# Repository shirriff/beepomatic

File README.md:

# beepomatic: automated backplane finding for Apollo-era hardware

This repository describes hardware and software for reverse-engineering a test box used with Apollo space hardware.
This is unlike to be useful to anyone else, but I figure I'll document it.

## Background

In the Apollo mission to the Moon, the [Up-Data Link](https://mobile.twitter.com/kenshirriff/status/1433169432709373953) was used to send data up to the spacecraft from
the ground.

To test the Up-Data Link, the [Up-Data Link Confidence Test Set](https://twitter.com/kenshirriff/status/1432411774985195527) was used.
Unfortunately, we can't find any documentation on this test box, so I'm reverse-engineering it.

The box consists of 25 circuit boards plugged into a wire-wrapped backplane. It's almost impossible to figure out how the boards are connected through this
tangle of wires. I beeped out some connections with a multimeter, but it is extremely tedious to do this manually through trial and error.
So I decided to automate the beeping process.

## Beep-o-matic

My idea was to build two boards that will automatically beep out the connections between them.
The idea is to pull one pin low and then see which other pins are pulled low on the other board; this indicates the pins are connected.

I still need to put boards into each combination of slots, so I need to run 300 scans. This is still somewhat tedious, but much better than probing the entire backplane
manually to find a single connection.

### Implementation

The backplane is implemented with 47-pin Elco connectors. Each board has three 16-bit GPIO chips connected to these pins; I used [PCA9555A](https://www.nxp.com/docs/en/data-sheet/PCA9555A.pdf) chips.)
The chips are driven over I2C from a Teensy microcontroller.
(Thanks to [PCBWay](https://www.pcbway.com/) for sponsoring these boards.)

On the software side, I wrote a simple program *beeper.ino*, which cycles through the 47 pins on each board, pulling each pin low in turn. It reads the remaining pins to see which ones are low
and outputs that data to the serial port. It takes under a second to perform this scan.

I run *beeper.py* on my laptop; it records the output for each scan in output files.

Finally, the program *net.py* processes these output files to find connected components and output the wiring nets.

### Issues

I pulled out all the boards, so I don't get any interference from the circuitry. However, the power and ground connections are still wired to the filter capacitors.
As a result, I see phantom connections between power and ground because of current flow through the capacitor. (This happens with multimeter beeping too.)
More inconvenient, though, is that once the capacitors are charged low, they can continue to pull the ground pins low even when I'm scanning unrelated pins.
This can make it appear that most pins are connected to ground. I filter this out in the software analysis.

A second problem is that the box has a lot of wiring to front panel switches, which are connected to power or ground (depending on their position).
I'll need to sort out that wiring manually.

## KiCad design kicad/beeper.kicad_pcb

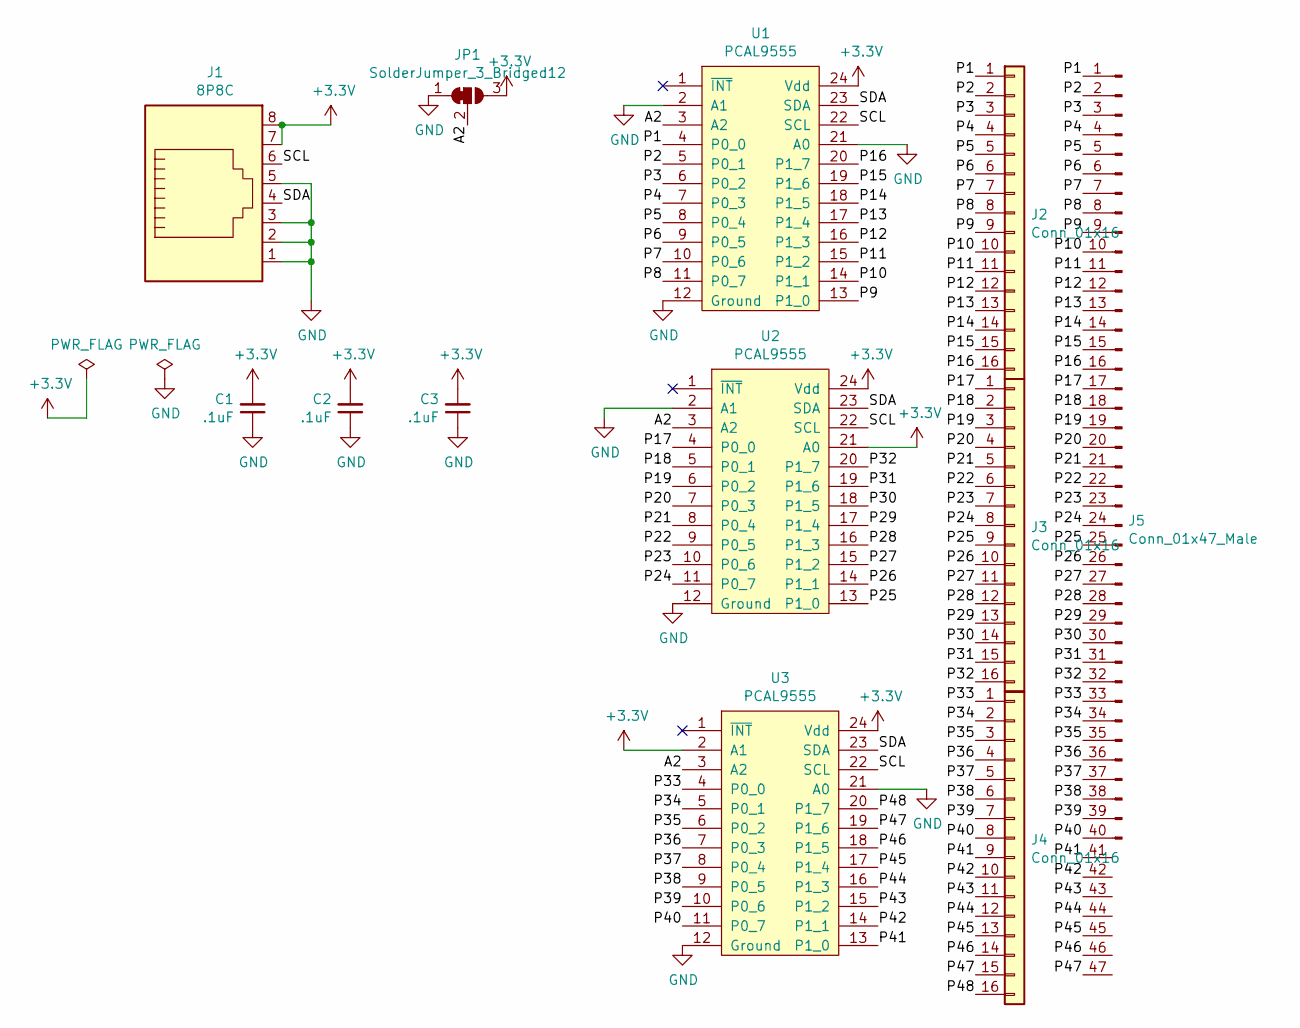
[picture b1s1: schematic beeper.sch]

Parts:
C1, C2, C3: .1uF; C_Disc_D3.0mm_W2.0mm_P2.50mm
J1: 8P8C; RJ45-8
J2, J3, J4: Conn_01x16; Pin_Header_Straight_1x16_Pitch2.54mm
J5: Conn_01x47_Male; elco-47
JP1: SolderJumper_3_Bridged12; SMT-JUMPER_3_NO_SILK
U1, U2, U3: PCAL9555; TSSOP-24_4.4x7.8mm_Pitch0.65mm

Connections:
+3V3: C1.2, C2.2, C3.2, J1.7, J1.8, JP1.3 (B), U1.24 (Vdd), U2.21 (A0), U2.24 (Vdd), U3.2 (A1), U3.24 (Vdd)
/A2: JP1.2 (C), U1.3 (A2), U2.3 (A2), U3.3 (A2)
/P1: J2.1, J5.1, U1.4 (P0_0)
/P2: J2.2, J5.2, U1.5 (P0_1)
/P3: J2.3, J5.3, U1.6 (P0_2)
/P4: J2.4, J5.4, U1.7 (P0_3)
/P5: J2.5, J5.5, U1.8 (P0_4)
/P6: J2.6, J5.6, U1.9 (P0_5)
/P7: J2.7, J5.7, U1.10 (P0_6)
/P8: J2.8, J5.8, U1.11 (P0_7)
/P9: J2.9, J5.9, U1.13 (P1_0)
/P10: J2.10, J5.10, U1.14 (P1_1)
/P11: J2.11, J5.11, U1.15 (P1_2)
/P12: J2.12, J5.12, U1.16 (P1_3)
/P13: J2.13, J5.13, U1.17 (P1_4)
/P14: J2.14, J5.14, U1.18 (P1_5)
/P15: J2.15, J5.15, U1.19 (P1_6)
/P16: J2.16, J5.16, U1.20 (P1_7)
/P17: J3.1, J5.17, U2.4 (P0_0)
/P18: J3.2, J5.18, U2.5 (P0_1)
/P19: J3.3, J5.19, U2.6 (P0_2)
/P20: J3.4, J5.20, U2.7 (P0_3)
/P21: J3.5, J5.21, U2.8 (P0_4)
/P22: J3.6, J5.22, U2.9 (P0_5)
/P23: J3.7, J5.23, U2.10 (P0_6)
/P24: J3.8, J5.24, U2.11 (P0_7)
/P25: J3.9, J5.25, U2.13 (P1_0)
/P26: J3.10, J5.26, U2.14 (P1_1)
/P27: J3.11, J5.27, U2.15 (P1_2)
/P28: J3.12, J5.28, U2.16 (P1_3)
/P29: J3.13, J5.29, U2.17 (P1_4)
/P30: J3.14, J5.30, U2.18 (P1_5)
/P31: J3.15, J5.31, U2.19 (P1_6)
/P32: J3.16, J5.32, U2.20 (P1_7)
/P33: J4.1, J5.33, U3.4 (P0_0)
/P34: J4.2, J5.34, U3.5 (P0_1)
/P35: J4.3, J5.35, U3.6 (P0_2)
/P36: J4.4, J5.36, U3.7 (P0_3)
/P37: J4.5, J5.37, U3.8 (P0_4)
/P38: J4.6, J5.38, U3.9 (P0_5)
/P39: J4.7, J5.39, U3.10 (P0_6)
/P40: J4.8, J5.40, U3.11 (P0_7)
/P41: J4.9, J5.41, U3.13 (P1_0)
/P42: J4.10, J5.42, U3.14 (P1_1)
/P43: J4.11, J5.43, U3.15 (P1_2)
/P44: J4.12, J5.44, U3.16 (P1_3)
/P45: J4.13, J5.45, U3.17 (P1_4)
/P46: J4.14, J5.46, U3.18 (P1_5)
/P47: J4.15, J5.47, U3.19 (P1_6)
/P48: J4.16, U3.20 (P1_7)
/SCL: J1.6, U1.22 (SCL), U2.22 (SCL), U3.22 (SCL)
/SDA: J1.4, U1.23 (SDA), U2.23 (SDA), U3.23 (SDA)
GND: C1.1, C2.1, C3.1, J1.1, J1.2, J1.3, J1.5, JP1.1 (A), U1.2 (A1), U1.12 (Ground), U1.21 (A0), U2.2 (A1), U2.12 (Ground), U3.12 (Ground), U3.21 (A0)

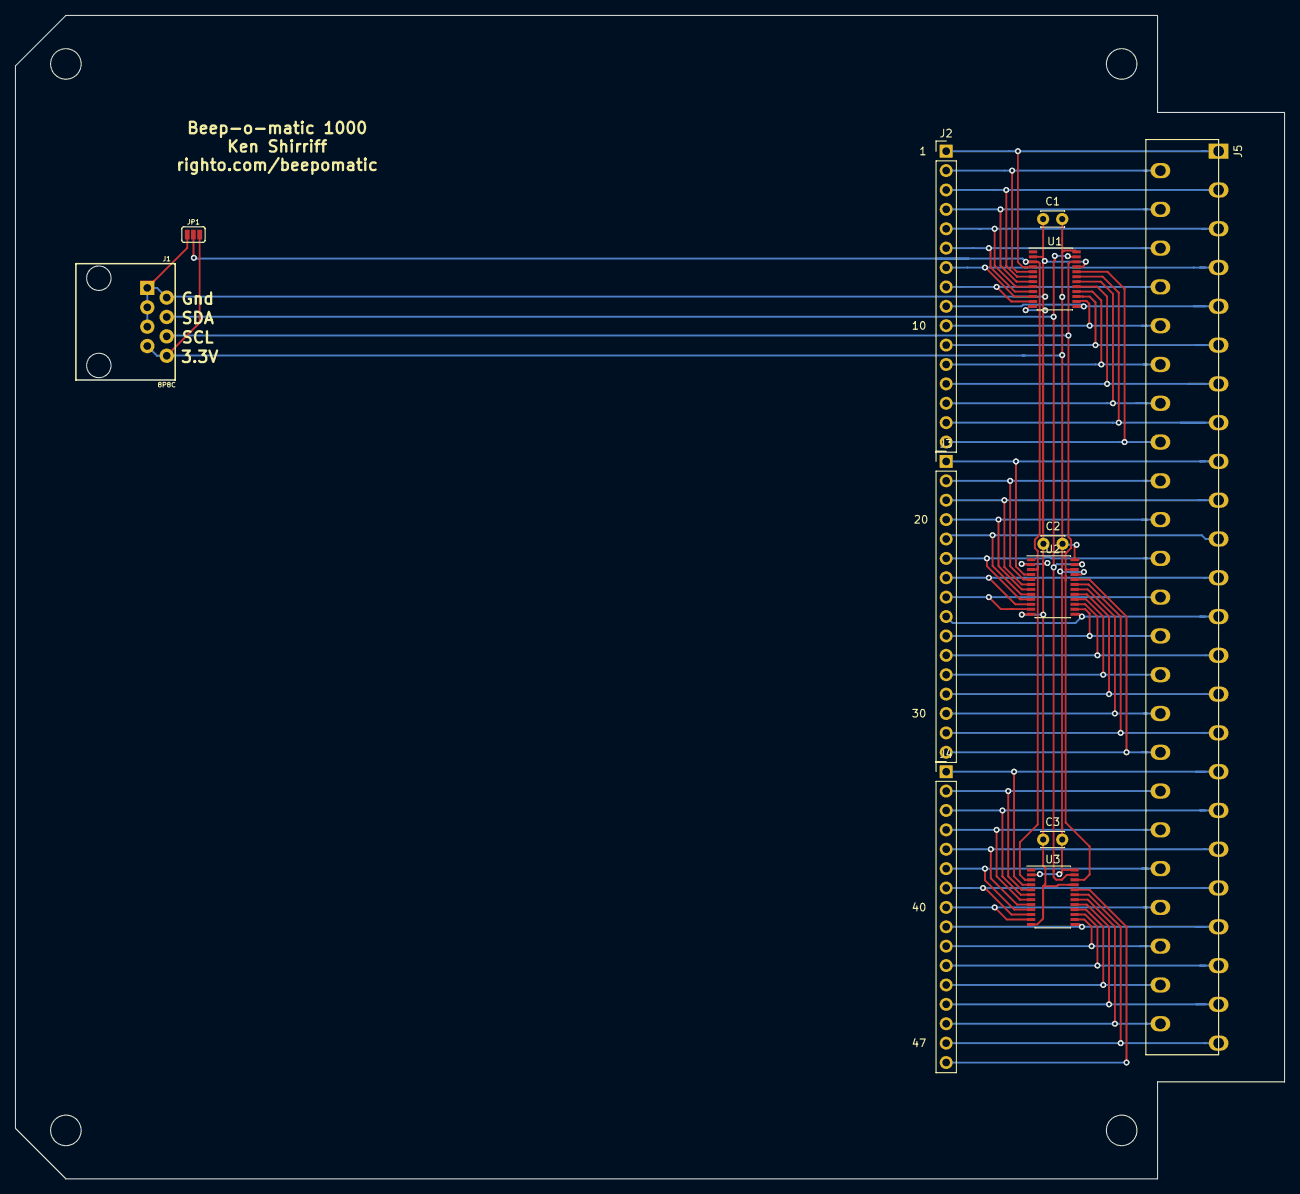
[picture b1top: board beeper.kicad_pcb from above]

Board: 2 copper layers, 166.2 x 152.4 mm, 12 parts (0 on the bottom side), 53 nets.

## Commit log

2021-11-01 Initial checkin
    Initial checkin of the hardware and software
2021-11-01 Add images to README.md
2021-11-01 Add .gitignore
2021-11-01 Create instructions.md
    instructions.md provides brief documentation on how to use the system.
2021-11-03 Program/sketch to detect external changes to pins.
2021-11-03 Bunch of improvements to net.py
2021-11-04 Add an image of the test setup.
2021-11-04 Update README.md
    Add an image and resize other images.
2022-01-28 Put a time delay so the program won't talk too much.
2022-01-28 Add fixlabels to check consistency
2022-01-28 Add software README
2022-01-30 Fix off-by-one error in pin ranges. Clean up input so fixlabels can be run multiple times.
